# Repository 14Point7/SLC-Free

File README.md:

SLC-Free
========

SLC Free is the only open source Wideband O2 Controller that works and is worth a damn

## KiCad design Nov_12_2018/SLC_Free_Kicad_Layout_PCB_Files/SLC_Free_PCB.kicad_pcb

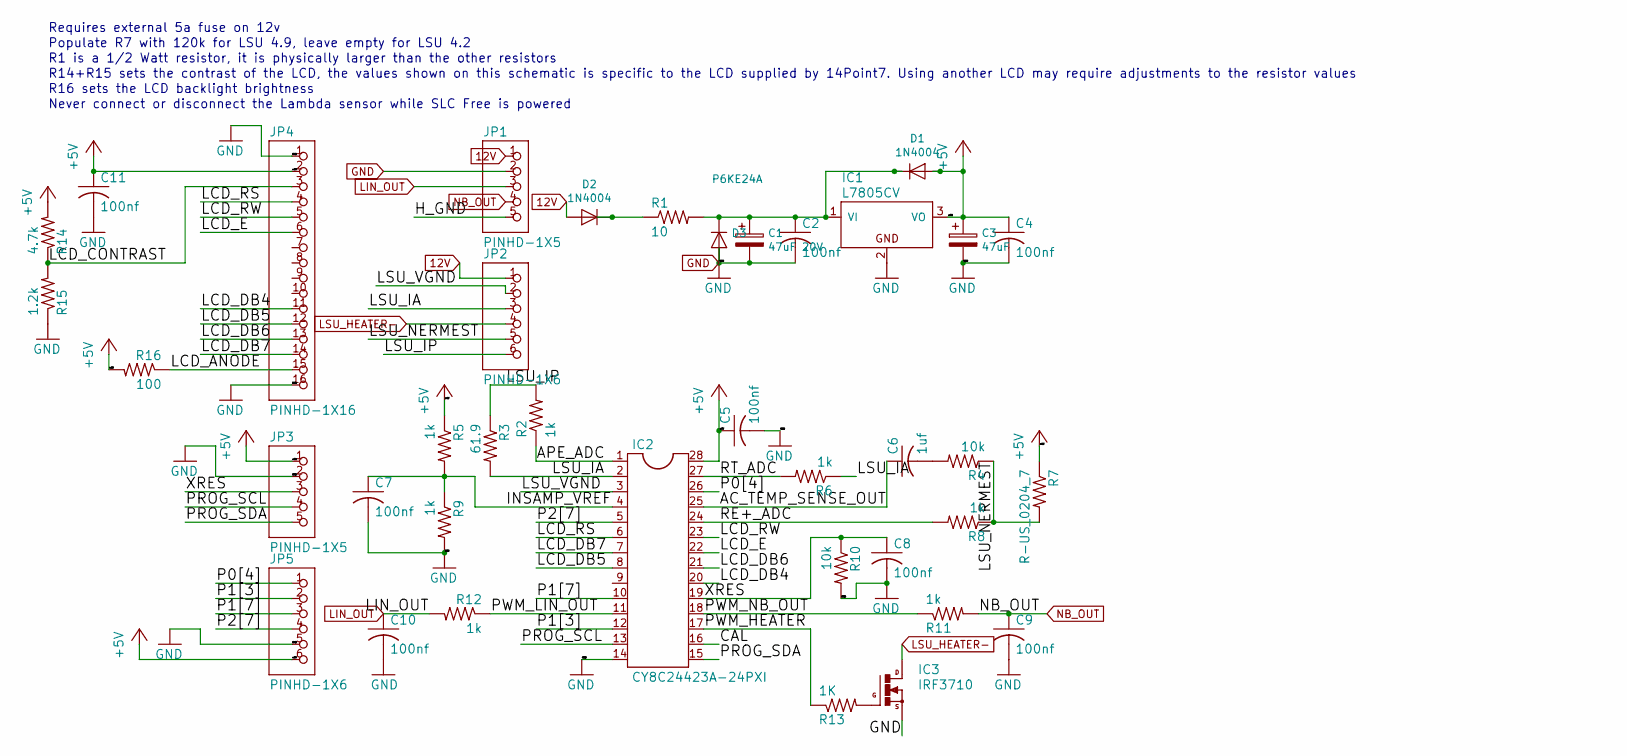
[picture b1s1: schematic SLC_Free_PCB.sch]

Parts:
C1: 47uF 20V; CP_Radial_D5.0mm_P2.50mm
C2, C4, C5, C7, C8, C9, C10, C11: 100nf; C025-025X050
C3: 47uF; CP_Radial_D5.0mm_P2.50mm
C6: 1uf; C025-025X050
D1, D2: 1N4004; D_DO-15_P10.16mm_Horizontal
D3: P6KE24A; D_DO-15_P10.16mm_Horizontal
IC1: L7805CV; TO220H
IC2: CY8C24423A-24PXI; DIL28-3
IC3: IRF3710; TO220BH
JP1: PINHD-1X5; Molex_Mega-Fit_76825-0004_2x02_P5.70mm_Horizontal
JP2: PINHD-1X6; Molex_Mega-Fit_76825-0006_2x03_P5.70mm_Horizontal
JP3: PINHD-1X5; 1X05
JP4: PINHD-1X16; 1X16
JP5: PINHD-1X6; 1X06
R1: 10; 0309_12
R2, R5, R6, R8, R9, R11, R12: 1k; 0204_7
R3: 61.9; 0204_7
R4, R10: 10k; 0204_7
R7: R-US_0204_7; 0204_7
R13: 1K; 0204_7
R14: 4.7k; 0204_7
R15: 1.2k; 0204_7
R16: 100; 0204_7

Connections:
12V: D2.2 (A), JP1.1, JP2.1
+5V: C3.1, C4.1, C5.1, C11.1, D1.2 (A), IC1.3 (VO), IC2.28, JP3.1, JP4.2, JP5.6, R5.1, R7.1, R14.2, R16.2
/AC_TEMP_SENSE_OUT: C6.1, IC2.25
/APE_ADC: IC2.1, R2.1
/CAL: IC2.16
/INSAMP_VREF: C7.1, IC2.4, R5.2, R9.1
/LCD_ANODE: JP4.15, R16.1
/LCD_CONTRAST: JP4.3, R14.1, R15.2
/LCD_DB4: IC2.20, JP4.11
/LCD_DB5: IC2.8, JP4.12
/LCD_DB6: IC2.21, JP4.13
/LCD_DB7: IC2.7, JP4.14
/LCD_E: IC2.22, JP4.6
/LCD_RS: IC2.6, JP4.4
/LCD_RW: IC2.23, JP4.5
/LSU_IA: IC2.2, JP2.3, R3.2, R6.1
/LSU_IP: JP2.6, R2.2, R3.1
/LSU_NERMEST: JP2.5, R4.1, R7.2, R8.1
/LSU_VGND: IC2.3, JP2.2
/P0[4]: IC2.26, JP5.1
/P1[3]: IC2.12, JP5.2
/P1[7]: IC2.10, JP5.3
/P2[7]: IC2.5, JP5.4
/PROG_SCL: IC2.13, JP3.4
/PROG_SDA: IC2.15, JP3.5
/PWM_HEATER: IC2.17, R13.1
/PWM_LIN_OUT: IC2.11, R12.1
/PWM_NB_OUT: IC2.18, R11.1
/RE+_ADC: IC2.24, R8.2
/RT_ADC: IC2.27, R6.2
/XRES: C8.1, IC2.19, JP3.3, R10.1
GND: C1.2, C2.2, C3.2, C4.2, C5.2, C7.2, C8.2, C9.2, C10.2, C11.2, D3.2 (A), IC1.2 (GND), IC2.14, IC3.S, JP1.2, JP3.2, JP4.1, JP4.16, JP5.5, R9.2, R10.2, R15.1
LIN_OUT: C10.1, JP1.3, R12.2
LSU_HEATER-: IC3.D, JP2.4
NB_OUT: C9.1, JP1.4, R11.2
unnamed: C1.1, C2.1, D1.1 (K), D3.1 (K), IC1.1 (VI), R1.2
unnamed: C6.2, R4.2
unnamed: D2.1 (K), R1.1
unnamed: IC3.G, R13.2

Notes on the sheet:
Requires external 5a fuse on 12v
Populate R7 with 120k for LSU 4.9, leave empty for LSU 4.2
R16 sets the LCD backlight brightness
R1 is a 1/2 Watt resistor, it is physically larger than the other resistors
R14+R15 sets the contrast of the LCD, the values shown on this schematic is specific to the LCD supplied by 14Point7. Using another LCD may require adjustments to the resistor values
Never connect or disconnect the Lambda sensor while SLC Free is powered

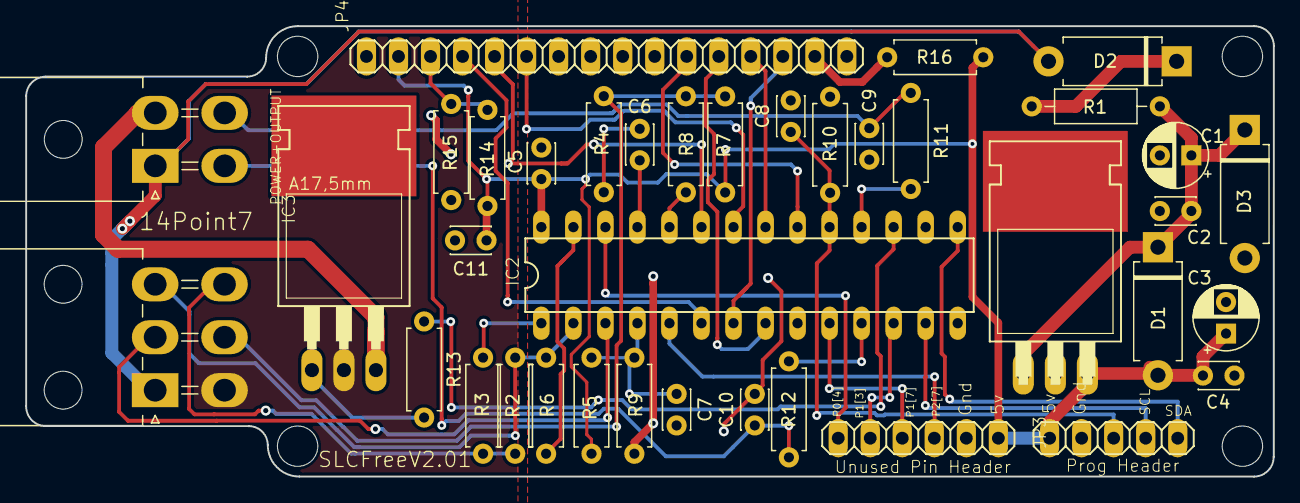
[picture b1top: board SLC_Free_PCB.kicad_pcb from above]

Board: 2 copper layers, 99.0 x 35.7 mm, 42 parts (0 on the bottom side), 38 nets.

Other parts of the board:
@HOLE0, @HOLE1, @HOLE2, @HOLE3: (no value)

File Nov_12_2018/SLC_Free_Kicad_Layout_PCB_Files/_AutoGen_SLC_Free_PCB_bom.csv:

Component,Description,Part,References,Value,Footprint,Quantity Per PCB,Datasheet
1,,C-US025-025X050,C2 C4 C5 C7 C8 C9 C10 C11,100nf,C025-025X050,8,
2,,C-US025-025X050,C6,1uf,C025-025X050,1,
3,Polarized capacitor,CP,C3,47uF,CP_Radial_D5.0mm_P2.50mm,1,~
4,Polarized capacitor,CP,C1,47uF 20V,CP_Radial_D5.0mm_P2.50mm,1,~
5,Diode,D,D1 D2,1N4004,D_DO-15_P10.16mm_Horizontal,2,~
6,Diode,D,D3,P6KE24A,D_DO-15_P10.16mm_Horizontal,1,~
7,,78T,IC1,78T,TO220H,1,
8,,DIL28-3,IC2,CY8C24423A-24PXI,DIL28-3,1,
9,,BUZ11BH,IC3,IRF3710,TO220BH,1,
10,,PINHD-1X16,JP4,PINHD-1X16,1X16,1,
11,,PINHD-1X5,JP1,PINHD-1X5,Molex_Mega-Fit_76825-0004_2x02_P5.70mm_Horizontal,1,
12,,PINHD-1X5,JP3,PINHD-1X5,1X05,1,
13,,PINHD-1X6,JP2,PINHD-1X6,Molex_Mega-Fit_76825-0006_2x03_P5.70mm_Horizontal,1,
14,,PINHD-1X6,JP5,PINHD-1X6,1X06,1,
15,,R-US_0204_7,R15,1.2k,0204_7,1,
16,,R-US_0309_12,R1,10,0309_12,1,
17,,R-US_0204_7,R16,100,0204_7,1,
18,,R-US_0204_7,R4 R10,10k,0204_7,2,
19,,R-US_0204_7,R2 R5 R6 R8 R9 R11 R12 R13,1k,0204_7,8,
20,,R-US_0204_7,R14,4.7k,0204_7,1,
21,,R-US_0204_7,R3,61.9,0204_7,1,
22,,R-US_0204_7,R7,R-US_0204_7,0204_7,1,





Component Groups:,22
Component Count:,38
Fitted Components:,38
Number of PCBs:,1
Total components:,38
Schematic Version:,
Schematic Date:,
BoM Date:,tor 28 mar 2019 13:11:28
Schematic Source:,/home/jp/Documents/KiCad/SLC_Free_PCB_V2/SLC_Free_PCB.sch
KiCad Version:,Eeschema 5.1.0-060a0da~80~ubuntu18.10.1

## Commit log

2013-12-19 Added SLC_Free_Manual
2019-08-21 New PCB & Firmware: Lambda and temp is displayed as text
